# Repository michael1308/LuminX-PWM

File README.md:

# LuminX-PWM
ESP32-based LED strip driver.

# Features
-   ESP32-WROOM-32E
-   CH340E/G
-   USB C
-   Micro USB for power
-   2.1mm Barrel Jack w/ reversible polarity    
-   Screw Terminal power input
-   Current Measurement w/ INA219/INA180
-   5V Buck Converter
-   3.3V LDO
-   Microphone
-   IR Receiver
-   5x PWM out
-   Power Switching Relay
-   Temperature Sensor DS18B20
-   I2C Connector
-   ESP32 Debug Connector
-   Up to 10A

# Rev 1.0 (03.2023)
## Issues:
- Reverse Polarity Protection MOSFET reversed
- INA180 Resistor too large -> change to 10mOhm
- USBLC6 wrong footprint -> SOT-6

## Changes:
- Remove Micro USB
- Route Input Voltage directly to output
- Change reverse polarity protection to antiparallel diode (M7)
- Better Integration for Temp Sensor
- Smaller Footprint
- Automotive or Glass fuse?

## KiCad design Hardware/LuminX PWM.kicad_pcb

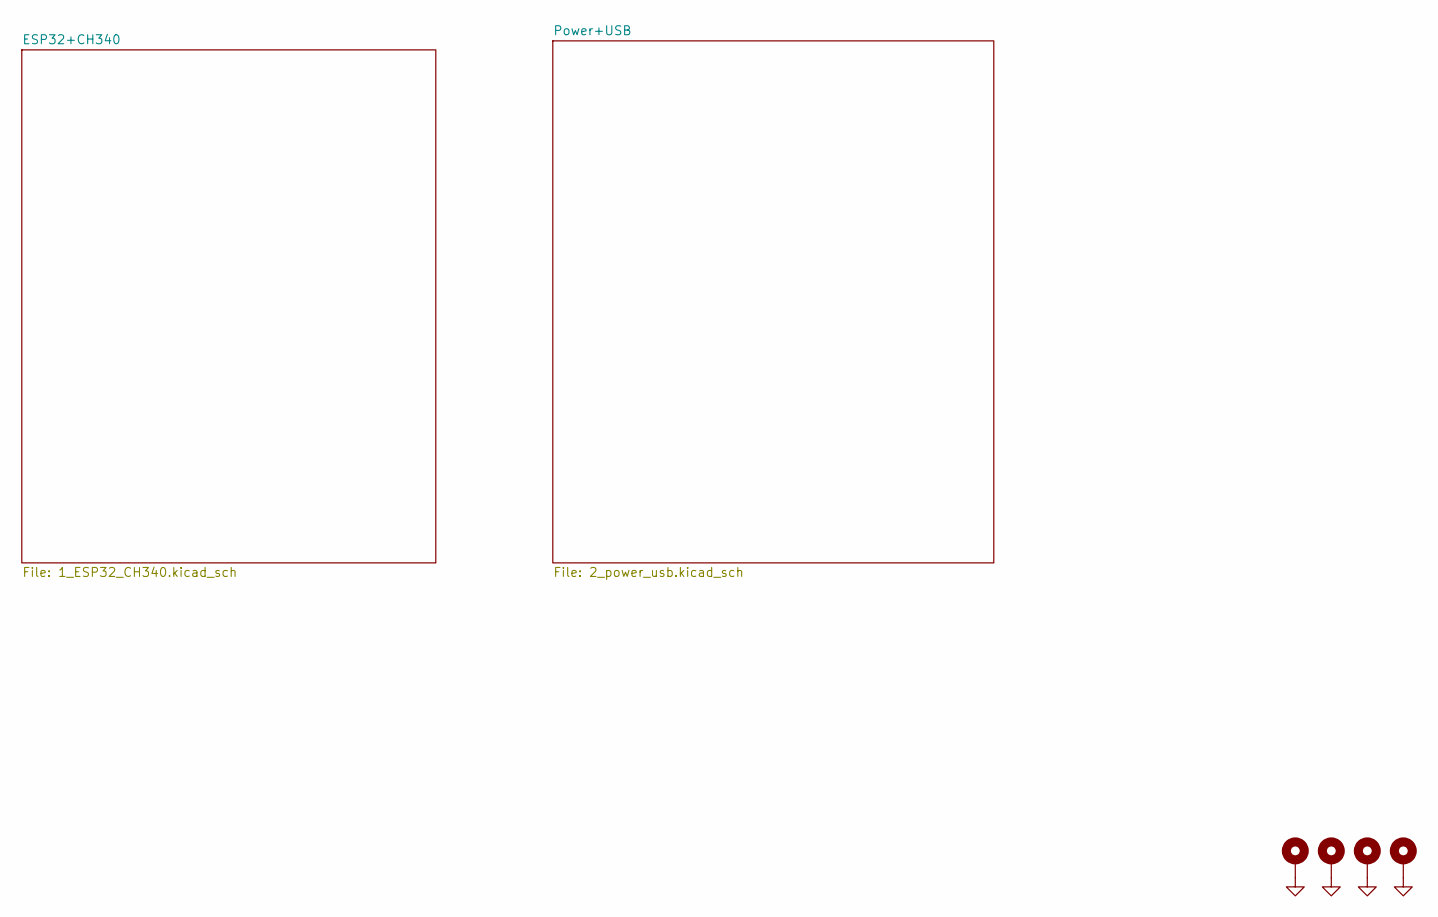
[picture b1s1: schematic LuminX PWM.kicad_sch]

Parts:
H1, H2, H3, H4: MountingHole; MountingHole_3.2mm_M3_Pad_Via

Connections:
GND: H1.1, H2.1, H3.1, H4.1; also elsewhere on the board

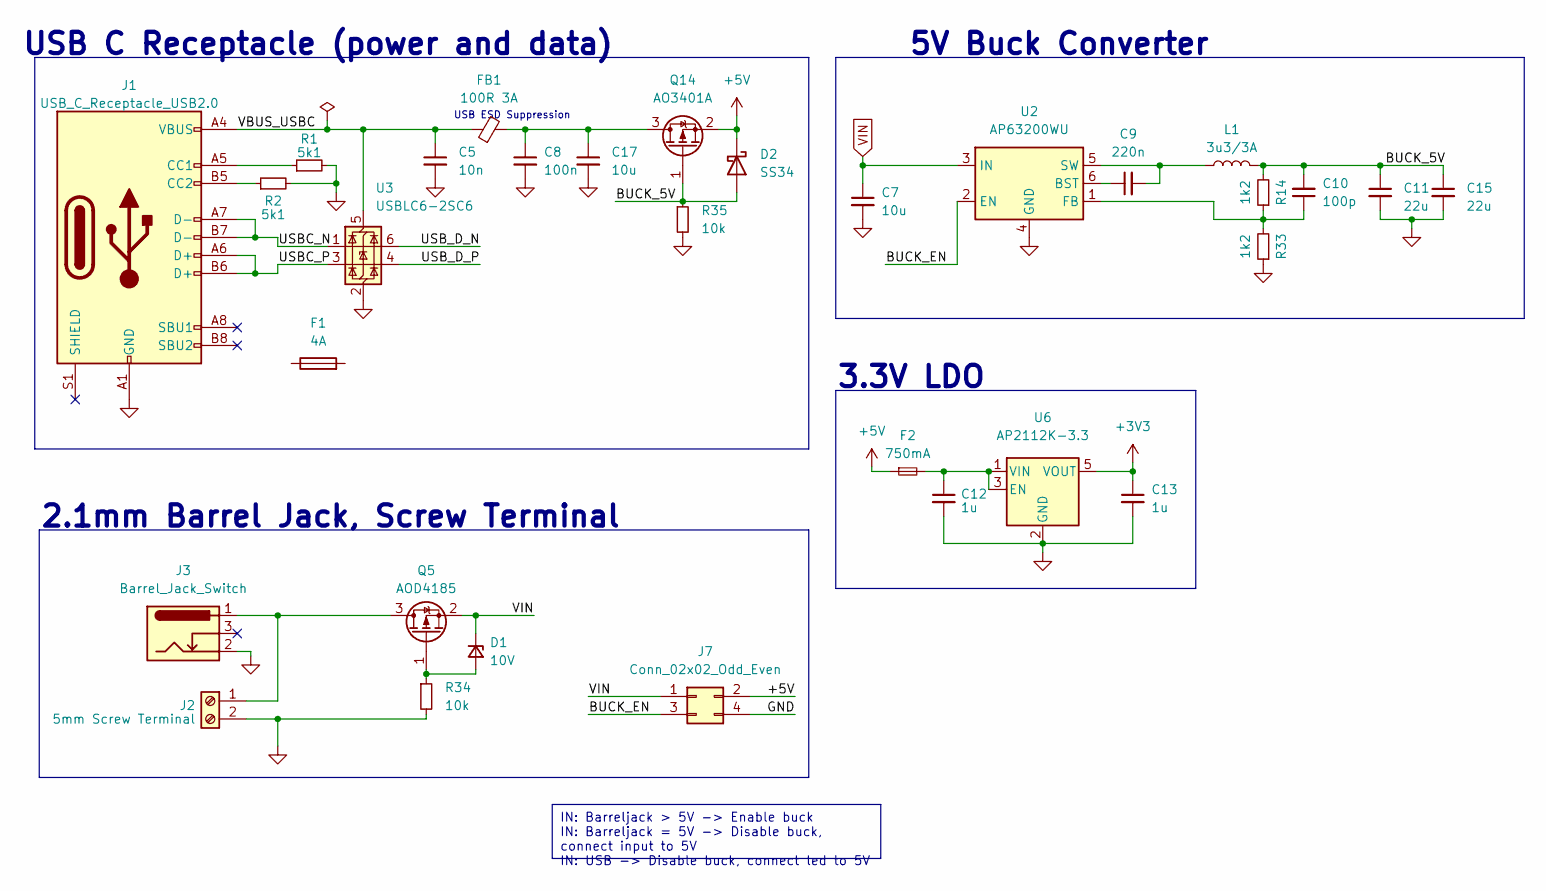
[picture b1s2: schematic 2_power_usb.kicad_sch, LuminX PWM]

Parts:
C5: 10n; C_0603_1608Metric
C7, C17: 10u; C_1206_3216Metric
C8: 100n; C_0603_1608Metric
C9: 220n; C_0603_1608Metric
C10: 100p; C_0603_1608Metric
C11, C15: 22u; C_1206_3216Metric
C12, C13: 1u; C_0603_1608Metric
D1: 10V
D2: SS34; D_SMA
F1: 4A
F2: 750mA
FB1: 100R 3A; L_0603_1608Metric
J1: USB_C_Receptacle_USB2.0; USB_C_Receptacle_HRO_TYPE-C-31-M-12
J2: 5mm Screw Terminal; TerminalBlock_Phoenix_MKDS-1,5-2_1x02_P5.00mm_Horizontal
J3: Barrel_Jack_Switch; BarrelJack_Horizontal
J7: Conn_02x02_Odd_Even
L1: 3u3/3A; L_TracoPower_TCK-047_5.2x5.8mm; Part No. SLH1207S330MTT
Q5: AOD4185; TO-252-2
Q14: AO3401A; SOT-23
R1, R2: 5k1; R_0603_1608Metric
R14, R33: 1k2; R_0603_1608Metric
R34, R35: 10k; R_0805_2012Metric
U2: AP63200WU; TSOT-23-6
U3: USBLC6-2SC6; SOT-23-6
U6: AP2112K-3.3; SOT-23-5

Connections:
/Power+USB/BUCK_5V: C10.2, C11.1, C15.1, D2.2 (A), L1.2, Q14.1 (G), R14.2, R35.1
/Power+USB/BUCK_EN: J7.3, U2.2 (EN)
/Power+USB/USBC_N: J1.A7 (D-), J1.B7 (D-), U3.1 (I/O1)
/Power+USB/USBC_P: J1.A6 (D+), J1.B6 (D+), U3.3 (I/O2)
/Power+USB/USB_D_N: U3.6 (I/O1)
/Power+USB/USB_D_P: U3.4 (I/O2)
GND: C5.2, C7.2, C8.2, C11.2, C12.2, C13.2, C15.2, C17.2, J1.A1 (GND), J1.A12 (GND), J1.B1 (GND), J1.B12 (GND), J2.2, J3.2, R1.2, R2.2, R33.1, R34.2, R35.2, U2.4 (GND), U3.2 (GND), U6.2 (GND); also elsewhere on the board
unnamed: J1.A5 (CC1), R1.1
unnamed: J1.B5 (CC2), R2.1
unnamed: J2.1, J3.1, Q5.3 (D)
unnamed: C8.1, C17.1, FB1.2, Q14.3 (D)
unnamed: C9.1, U2.6 (BST)
unnamed: C10.1, R14.1, R33.2, U2.1 (FB)
unnamed: C9.2, L1.1, U2.5 (SW)
unnamed: C12.1, F2.2, U6.1 (VIN), U6.3 (EN)
VIN: C7.1, U2.3 (IN)

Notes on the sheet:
IN: Barreljack > 5V -> Enable buck IN: Barreljack = 5V -> Disable buck, connect input to 5V IN: USB -> Disable buck, connect led to 5V
3.3V LDO
USB ESD Suppression
5V Buck Converter
USB C Receptacle (power and data)
2.1mm Barrel Jack, Screw Terminal

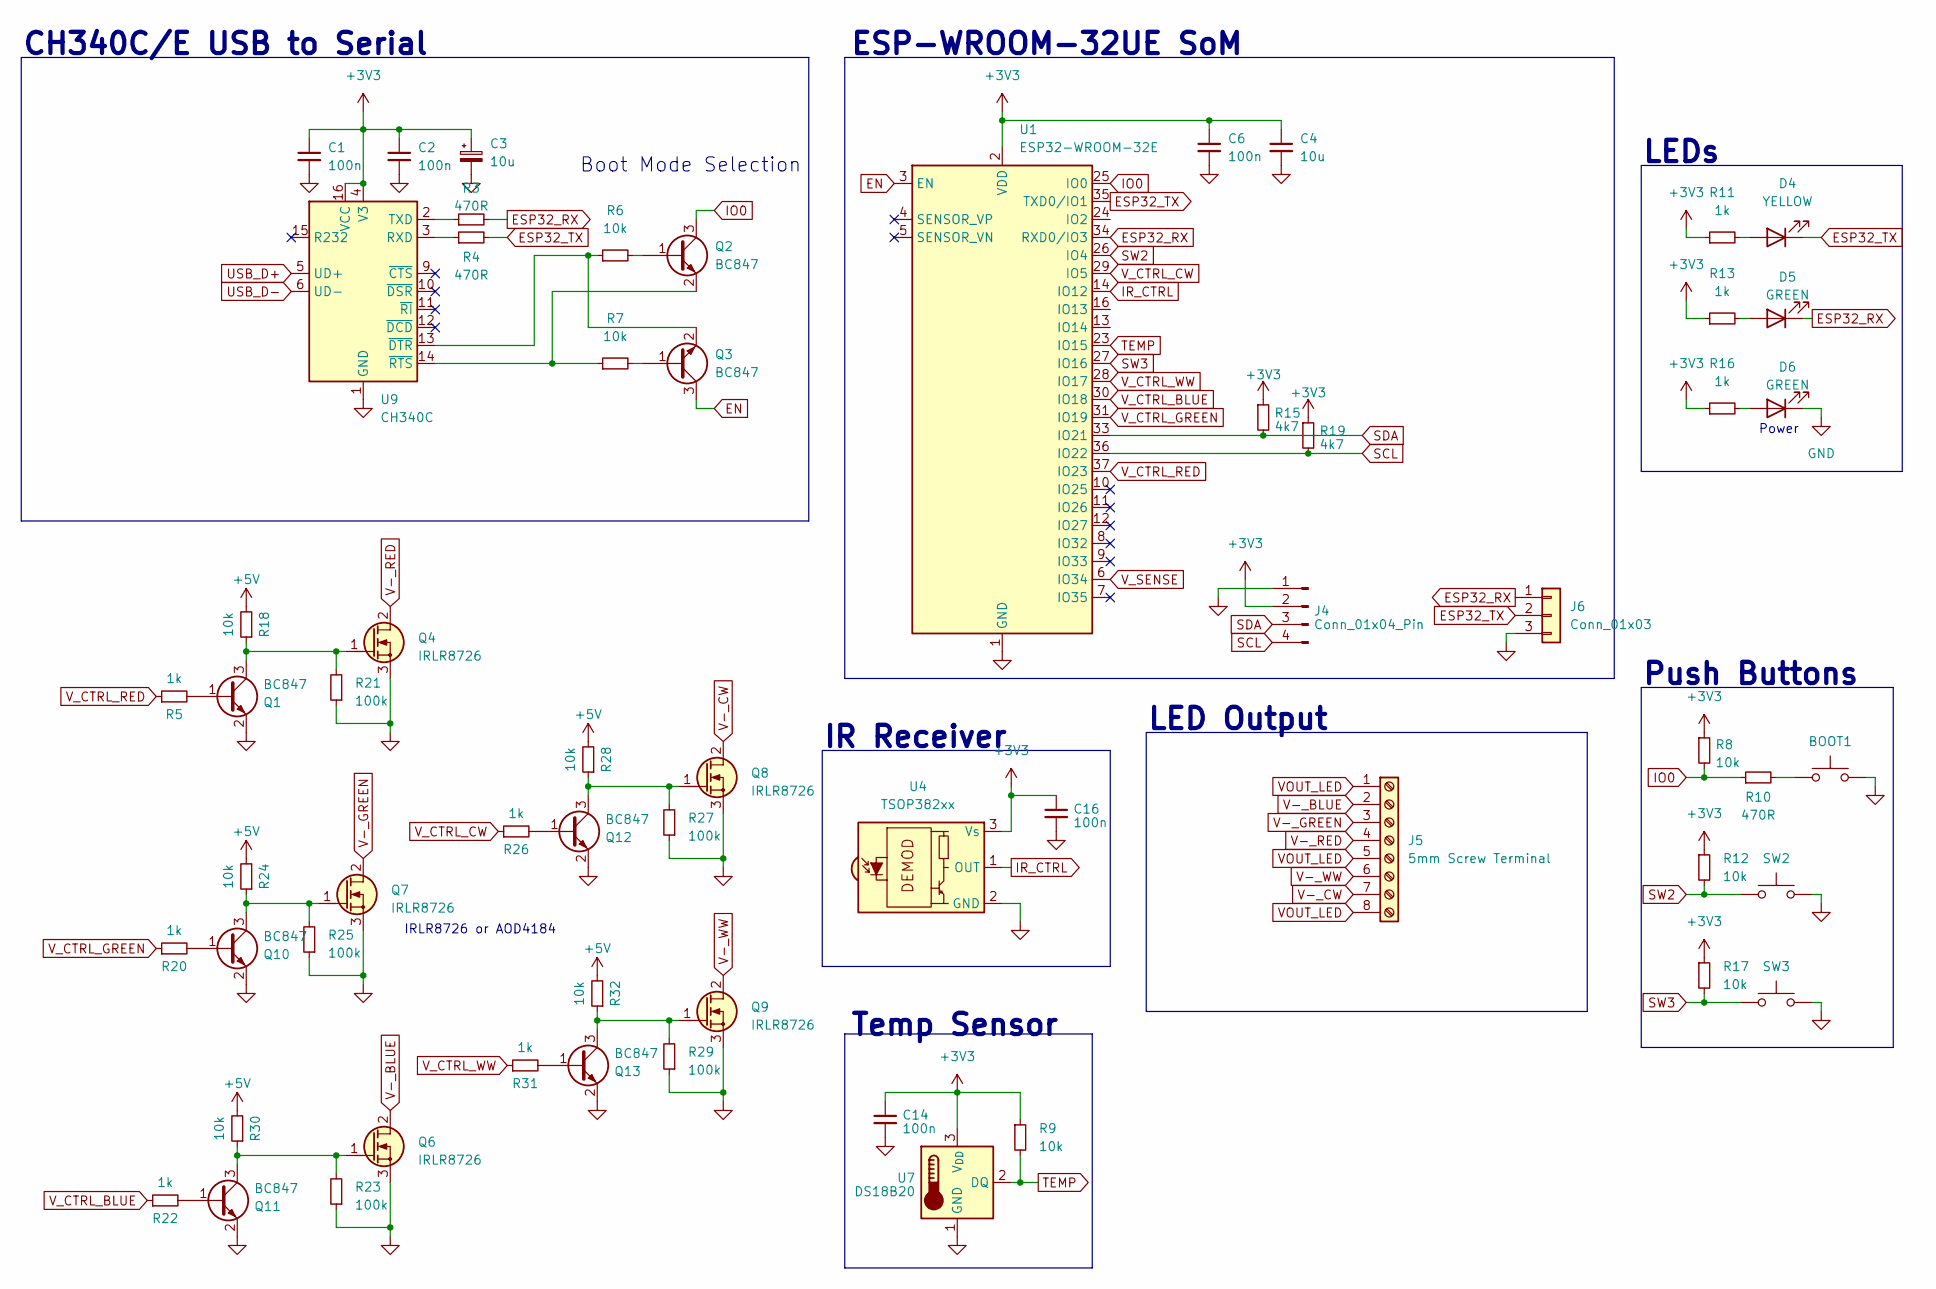
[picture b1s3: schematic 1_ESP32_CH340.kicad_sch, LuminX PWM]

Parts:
BOOT1: SW_Push; SW_SPST_PTS645
C1, C2, C6, C14, C16: 100n; C_0603_1608Metric
C3: 10u; C_0805_2012Metric
C4: 10u
D4: YELLOW; LED_1206_3216Metric_ReverseMount_Hole1.8x2.4mm
D5, D6: GREEN; LED_1206_3216Metric_ReverseMount_Hole1.8x2.4mm
J4: Conn_01x04_Pin; JST_SH_BM04B-SRSS-TB_1x04-1MP_P1.00mm_Vertical
J5: 5mm Screw Terminal; TerminalBlock_Phoenix_MKDS-1,5-8_1x08_P5.00mm_Horizontal
J6: Conn_01x03
Q1, Q2, Q3, Q10, Q11, Q12, Q13: BC847; SOT-23
Q4, Q6, Q7, Q8, Q9: IRLR8726; TO-252-2
R3, R4, R10: 470R; R_0603_1608Metric
R5, R11, R13, R16, R20, R22, R26, R31: 1k; R_0603_1608Metric
R6, R7, R8, R9, R12, R17, R18, R24, R28, R30, R32: 10k; R_0603_1608Metric
R15, R19: 4k7; R_0603_1608Metric
R21, R23, R25, R27, R29: 100k; R_0603_1608Metric
SW2, SW3: SW_Push; SW_SPST_PTS645
U1: ESP32-WROOM-32E; ESP32-WROOM-32D
U4: TSOP382xx; Vishay_MINICAST-3Pin
U7: DS18B20; TO-92_Inline
U9: CH340C; SOIC-16_3.9x9.9mm_P1.27mm

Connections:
EN: Q3.3 (C), U1.3 (EN)
ESP32_RX: D5.1 (K), J6.1, R3.2, U1.34 (RXD0/IO3)
ESP32_TX: D4.1 (K), J6.2, R4.2, U1.35 (TXD0/IO1)
GND: BOOT1.2, C1.2, C2.2, C3.2, C4.2, C6.2, C14.2, C16.2, D6.1 (K), J4.1, J6.3, Q1.2 (E), Q4.3 (S), Q6.3 (S), Q7.3 (S), Q8.3 (S), Q9.3 (S), Q10.2 (E), Q11.2 (E), Q12.2 (E), Q13.2 (E), R21.1, R23.1, R25.1, R27.1, R29.1, SW2.2, SW3.2, U1.1 (GND), U1.15 (GND), U1.38 (GND), U1.39 (GND), U4.2 (GND), U7.1 (GND), U9.1 (GND); also elsewhere on the board
IO0: Q2.3 (C), R8.2, R10.1, U1.25 (IO0)
IR_CTRL: U1.14 (IO12), U4.1 (OUT)
unnamed: BOOT1.1, R10.2
unnamed: D4.2 (A), R11.2
unnamed: D5.2 (A), R13.2
unnamed: D6.2 (A), R16.2
unnamed: Q1.1 (B), R5.2
unnamed: Q1.3 (C), Q4.1 (G), R18.1, R21.2
unnamed: Q2.1 (B), R6.2
unnamed: Q2.2 (E), R7.1, U9.14 (~RTS)
unnamed: Q3.1 (B), R7.2
unnamed: Q3.2 (E), R6.1, U9.13 (~DTR)
unnamed: Q10.1 (B), R20.2
unnamed: Q7.1 (G), Q10.3 (C), R24.1, R25.2
unnamed: Q11.1 (B), R22.2
unnamed: Q6.1 (G), Q11.3 (C), R23.2, R30.1
unnamed: Q12.1 (B), R26.2
unnamed: Q8.1 (G), Q12.3 (C), R27.2, R28.1
unnamed: Q13.1 (B), R31.2
unnamed: Q9.1 (G), Q13.3 (C), R29.2, R32.1
unnamed: R4.1, U9.3 (RXD)
unnamed: R3.1, U9.2 (TXD)
SCL: J4.4, R19.2, U1.36 (IO22)
SDA: J4.3, R15.2, U1.33 (IO21)
SW2: R12.2, SW2.1, U1.26 (IO4)
SW3: R17.2, SW3.1, U1.27 (IO16)
TEMP: R9.2, U1.23 (IO15), U7.2 (DQ)
USB_D+: U9.5 (UD+)
USB_D-: U9.6 (UD-)
V-_BLUE: J5.2, Q6.2 (D)
V-_CW: J5.7, Q8.2 (D)
V-_GREEN: J5.3, Q7.2 (D)
V-_RED: J5.4, Q4.2 (D)
V-_WW: J5.6, Q9.2 (D)
VOUT_LED: J5.1, J5.5, J5.8
V_CTRL_BLUE: R22.1, U1.30 (IO18)
V_CTRL_CW: R26.1, U1.29 (IO5)
V_CTRL_GREEN: R20.1, U1.31 (IO19)
V_CTRL_RED: R5.1, U1.37 (IO23)
V_CTRL_WW: R31.1, U1.28 (IO17)
V_SENSE: U1.6 (IO34)

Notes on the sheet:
IR Receiver
Push Buttons
Power
Boot Mode Selection
Temp Sensor
CH340C/E USB to Serial
LEDs
ESP-WROOM-32UE SoM
LED Output
IRLR8726 or AOD4184

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
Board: 4 copper layers, 92 parts (8 on the bottom side), 58 nets, no tracks yet.

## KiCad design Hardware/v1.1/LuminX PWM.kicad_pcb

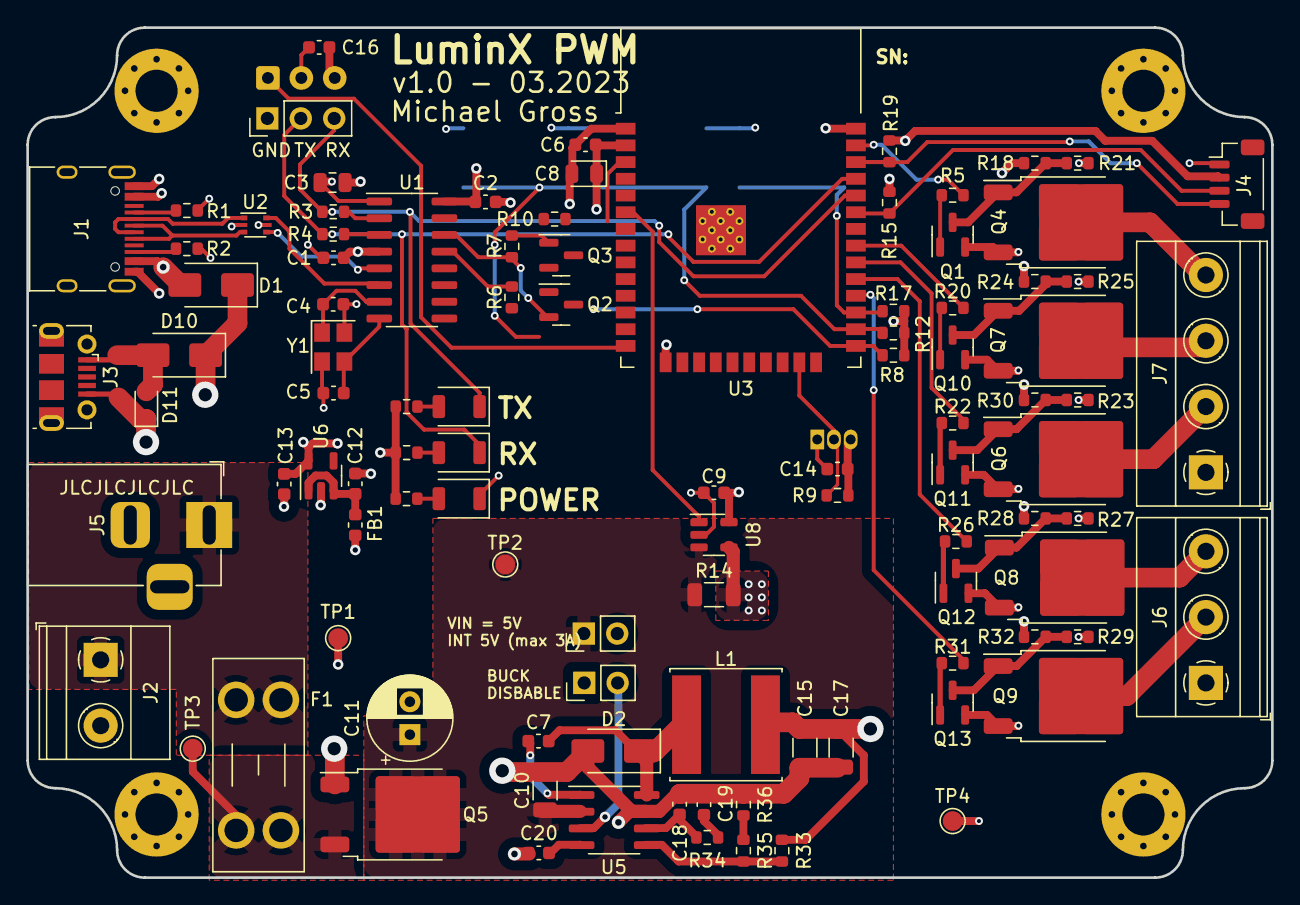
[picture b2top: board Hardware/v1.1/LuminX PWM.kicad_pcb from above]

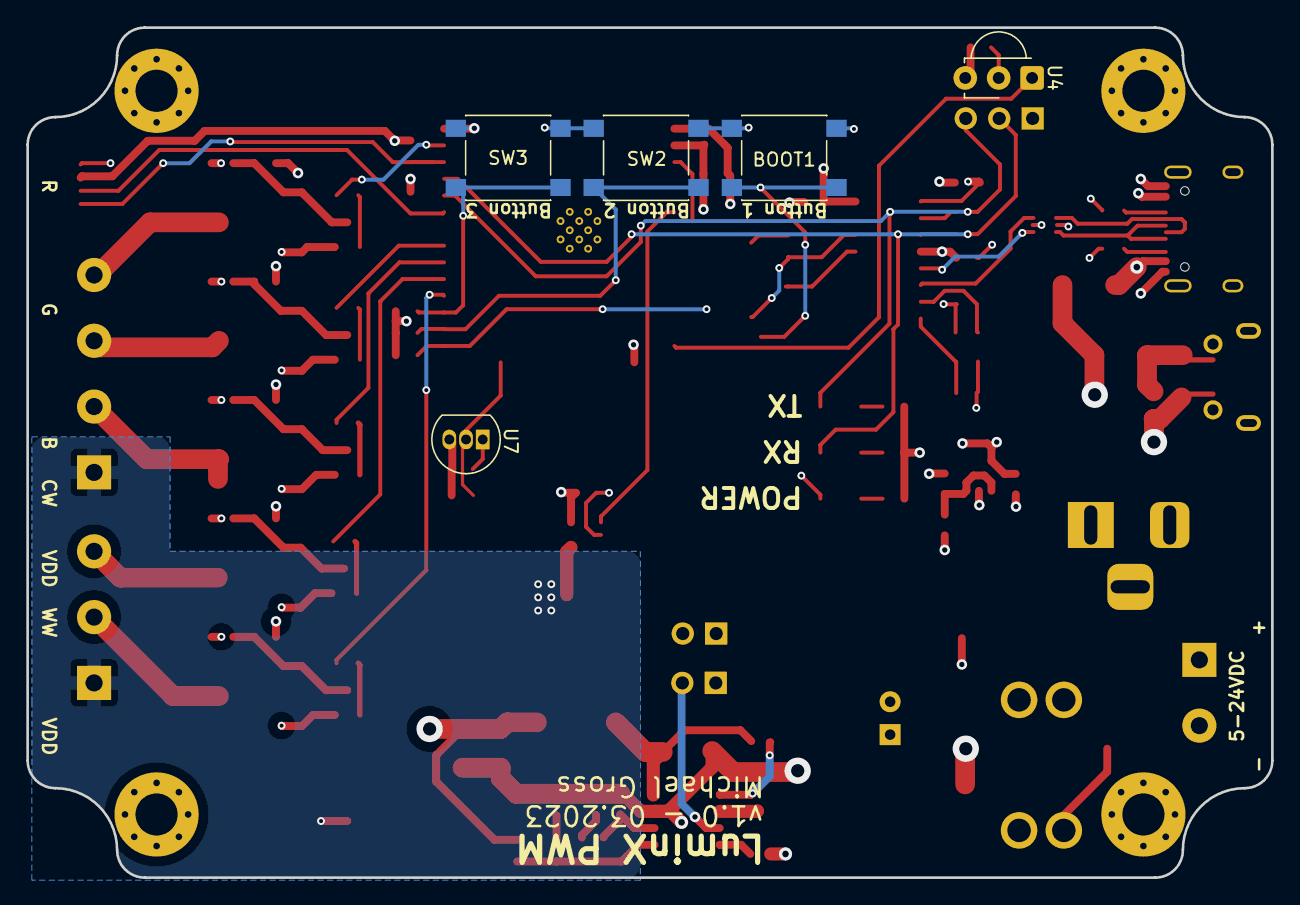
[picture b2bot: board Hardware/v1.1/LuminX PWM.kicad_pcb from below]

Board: 4 copper layers, 94.6 x 64.6 mm, 109 parts (5 on the bottom side), 67 nets.

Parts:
BOOT1: SW_Push; SW_SPST_PTS645
C1, C2, C6, C7, C9, C14, C16: 100n; C_0603_1608Metric
C3: 10u; C_0805_2012Metric
C4, C5: 30p; C_0603_1608Metric
C8: 10u; D_0805_2012Metric
C10: 10u; C_1206_3216Metric
C11: 100u/35V; CP_Radial_D6.3mm_P2.50mm
C12, C13: 1u; C_0603_1608Metric
C15, C17: 22u; C_1206_3216Metric
C18: 10p; C_0603_1608Metric
C19: 1n; C_0603_1608Metric
C20: 8n2; C_0603_1608Metric
D1, D10: SS34; D_SMA
D2: SS54; D_SMA
D4: YELLOW; LED_1206_3216Metric_ReverseMount_Hole1.8x2.4mm
D5, D6: GREEN; LED_1206_3216Metric_ReverseMount_Hole1.8x2.4mm
D11: SD12C; D_SOD-323
F1: 10A; Fuseholder_Blade_Mini_Keystone_3568
FB1: 100R; L_0603_1608Metric
H1, H2, H3, H4: MountingHole; MountingHole_3.2mm_M3_Pad_Via
J1: USB_C_Receptacle_USB2.0; USB_C_Receptacle_HRO_TYPE-C-31-M-12
J2: 5mm Screw Terminal; TerminalBlock_Phoenix_MKDS-1,5-2_1x02_P5.00mm_Horizontal
J3: USB_B_Micro; USB_Micro-B_Molex-105017-0001
J4: Conn_01x04_Pin; JST_SH_BM04B-SRSS-TB_1x04-1MP_P1.00mm_Vertical
J5: Barrel_Jack_Switch; BarrelJack_Horizontal
J6: Screw_Terminal_01x03; TerminalBlock_Phoenix_MKDS-1,5-3_1x03_P5.00mm_Horizontal
J7: 5mm Screw Terminal; TerminalBlock_Phoenix_MKDS-1,5-4_1x04_P5.00mm_Horizontal
J9: Conn_01x03_Pin; PinHeader_1x03_P2.54mm_Vertical
JP1, JP3: Jumper_2_Open; PinHeader_1x02_P2.54mm_Vertical
L1: 10u/3A; L_Sunlord_SWPA8040S
Q1, Q2, Q3, Q10, Q11, Q12, Q13: BC847; SOT-23
Q4, Q6, Q7, Q8, Q9: IRLR8726; TO-252-2
Q5: WSF70P03; TO-252-2
R1, R2: 5k1; R_0603_1608Metric
R3, R4, R10: 470R; R_0603_1608Metric
R5, R11, R13, R16, R20, R22, R26, R31: 1k; R_0603_1608Metric
R6, R7, R8, R9, R12, R17, R18, R24, R28, R30, R32, R33: 10k; R_0603_1608Metric
R14: 0.1R; R_1206_3216Metric
R15, R19: 4k7; R_0603_1608Metric
R21, R23, R25, R27, R29: 100k; R_0603_1608Metric
R34: 33k; R_0603_1608Metric
R35: 1k2; R_0603_1608Metric
R36: 680; R_0603_1608Metric
SW2, SW3: SW_Push; SW_SPST_PTS645
TP1, TP2, TP3, TP4: TestPoint; TestPoint_Pad_D1.5mm
U1: CH340G; SOIC-16_3.9x9.9mm_P1.27mm
U2: USBLC6-2P6; SOT-666
U3: ESP32-WROOM-32D
U4: TSOP382xx; Vishay_MINICAST-3Pin
U5: TPS54332; SOIC-8_3.9x4.9mm_P1.27mm
U6: AP2112K-3.3; SOT-23-5
U7: DS18B20; TO-92_Inline
U8: INA180A1; SOT-23-5
Y1: 12MHz; Crystal_SMD_3225-4Pin_3.2x2.5mm

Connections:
+3V3: C1.1, C2.1, C3.1, C6.1, C8.1, C9.1, C13.1, C14.1, C16.1, J4.2, R8.1, R9.1, R11.1, R12.1, R13.1, R15.1, R16.1, R17.1, R19.1, U1.4 (V3), U1.16 (VCC), U3.2 (VDD), U4.3 (Vs), U6.5 (VOUT), U7.3 (V_{DD}), U8.5 (V+)
+5V: C15.1, C17.1, D1.1 (K), D10.1 (K), FB1.1, JP3.2 (B), L1.2, R18.2, R24.2, R28.2, R30.2, R32.2, R33.2, TP1.1
/ESP32+CH340/CH340_XI: C4.1, U1.7 (XI), Y1.1
/ESP32+CH340/CH340_XO: C5.1, U1.8 (XO), Y1.3
/ESP32+CH340/nDTR: Q3.2 (E), U1.13 (~DTR)
/ESP32+CH340/nRTS: Q2.2 (E), R7.1, U1.14 (~RTS)
/Power+USB/D+: J1.A6 (D+), J1.B6 (D+), U2.3 (I/O2)
/Power+USB/D-: J1.A7 (D-), J1.B7 (D-), U2.1 (I/O1)
/Power+USB/VBUS_MICROUSB: D10.2 (A), D11.2 (A2), J3.1 (VBUS)
/Power+USB/VBUS_USBC: D1.2 (A), J1.A4 (VBUS), J1.A9 (VBUS), J1.B4 (VBUS), J1.B9 (VBUS), U2.5 (VBUS)
/Power+USB/VIN_RAW: F1.1, J2.1, J5.1
/Power+USB/VIN_RPP: F1.2, Q5.3 (S), TP3.1
EN: Q2.3 (C), U3.3 (EN)
ESP32_RX: D5.1 (K), J9.3, R3.2, U3.34 (RXD0/IO3)
ESP32_TX: D4.1 (K), J9.2, R4.2, U3.35 (TXD0/IO1)
GND: BOOT1.2, C1.2, C2.2, C3.2, C4.2, C5.2, C6.2, C8.2, C9.2, C10.2, C11.2, C12.2, C13.2, C14.2, C15.2, C16.2, C17.2, C18.2, C19.2, C20.2, D2.2 (A), D6.1 (K), D11.1 (A1), H1.1, H2.1, H3.1, H4.1, J1.A1 (GND), J1.A12 (GND), J1.B1 (GND), J1.B12 (GND), J2.2, J3.5 (GND), J4.1, J5.2, J9.1, JP1.1 (A), Q1.2 (E), Q4.3 (S), Q5.1 (G), Q6.3 (S), Q7.3 (S), Q8.3 (S), Q9.3 (S), Q10.2 (E), Q11.2 (E), Q12.2 (E), Q13.2 (E), R1.2, R2.2, R21.1, R23.1, R25.1, R27.1, R29.1, R36.1, SW2.2, SW3.2, U1.1 (GND), U2.2 (GND), U3.1 (GND), U3.15 (GND), U3.38 (GND), U3.39 (GND), U4.2 (GND), U5.7 (GND), U6.2 (GND), U7.1 (GND), U8.2 (GND), Y1.2, Y1.4
IO0: Q3.3 (C), R8.2, R10.1, U3.25 (IO0)
IR_CTRL: U3.14 (IO12), U4.1 (OUT)
unnamed: BOOT1.1, R10.2
unnamed: C19.1, R34.1
unnamed: C7.2, D2.1 (K), L1.1, U5.8 (PH)
unnamed: D4.2 (A), R11.2
unnamed: D5.2 (A), R13.2
unnamed: D6.2 (A), R16.2
unnamed: J1.A5 (CC1), R1.1
unnamed: J1.B5 (CC2), R2.1
unnamed: JP1.2 (B), U5.3 (EN)
unnamed: Q1.1 (B), R5.2
unnamed: Q1.3 (C), Q4.1 (G), R18.1, R21.2
unnamed: Q2.1 (B), R6.2
unnamed: Q3.1 (B), R7.2
unnamed: Q10.1 (B), R20.2
unnamed: Q7.1 (G), Q10.3 (C), R24.1, R25.2
unnamed: Q11.1 (B), R22.2
unnamed: Q6.1 (G), Q11.3 (C), R23.2, R30.1
unnamed: Q12.1 (B), R26.2
unnamed: Q8.1 (G), Q12.3 (C), R27.2, R28.1
unnamed: Q13.1 (B), R31.2
unnamed: Q9.1 (G), Q13.3 (C), R29.2, R32.1
unnamed: R35.1, R36.2
unnamed: R4.1, U1.3 (RXD)
unnamed: R3.1, U1.2 (TXD)
unnamed: C7.1, U5.1 (BOOT)
unnamed: C18.1, R34.2, U5.6 (COMP)
unnamed: C20.1, U5.4 (SS)
unnamed: R33.1, R35.2, U5.5 (VSENSE)
unnamed: C12.1, FB1.2, U6.1 (VIN), U6.3 (EN)
SCL: J4.4, R19.2, U3.36 (IO22)
SDA: J4.3, R15.2, U3.33 (IO21)
SW2: R12.2, SW2.1, U3.26 (IO4)
SW3: R17.2, SW3.1, U3.27 (IO16)
TEMP: R9.2, U3.23 (IO15), U7.2 (DQ)
USB_D+: U1.5 (UD+), U2.4 (I/O2)
USB_D-: U1.6 (UD-), U2.6 (I/O1)
V-_BLUE: J7.2, Q6.2 (D)
V-_CW: J6.3, Q8.2 (D)
V-_GREEN: J7.3, Q7.2 (D)
V-_RED: J7.4, Q4.2 (D)
V-_WW: J6.2, Q9.2 (D)
VIN: C10.1, C11.1, JP3.1 (A), Q5.2 (D), R14.1, TP2.1, U5.2 (VIN), U8.3 (+)
VOUT_LED: J6.1, J7.1, R14.2, TP4.1, U8.4 (-)
V_CTRL_BLUE: R22.1, U3.30 (IO18)
V_CTRL_CW: R26.1, U3.29 (IO5)
V_CTRL_GREEN: R20.1, U3.31 (IO19)
V_CTRL_RED: R5.1, U3.37 (IO23)
V_CTRL_WW: R31.1, U3.28 (IO17)
V_SENSE: U3.6 (IO34), U8.1

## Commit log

2023-04-01 Rev 1.0
2023-11-24 Restructure project
2024-12-14 Update backups
2024-12-15 Add backups
2025-02-23 refactor
2025-02-23 Add enclosure files
